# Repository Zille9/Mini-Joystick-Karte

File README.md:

# Mini-Joystick-Karte
Joystickkarte für den HIVE-Retrostyle-Computer
Anschluss erfolgt am I2C-BUS des HIVE (PIN18 SCL und PIN19 SDA vom Administra-Chip)

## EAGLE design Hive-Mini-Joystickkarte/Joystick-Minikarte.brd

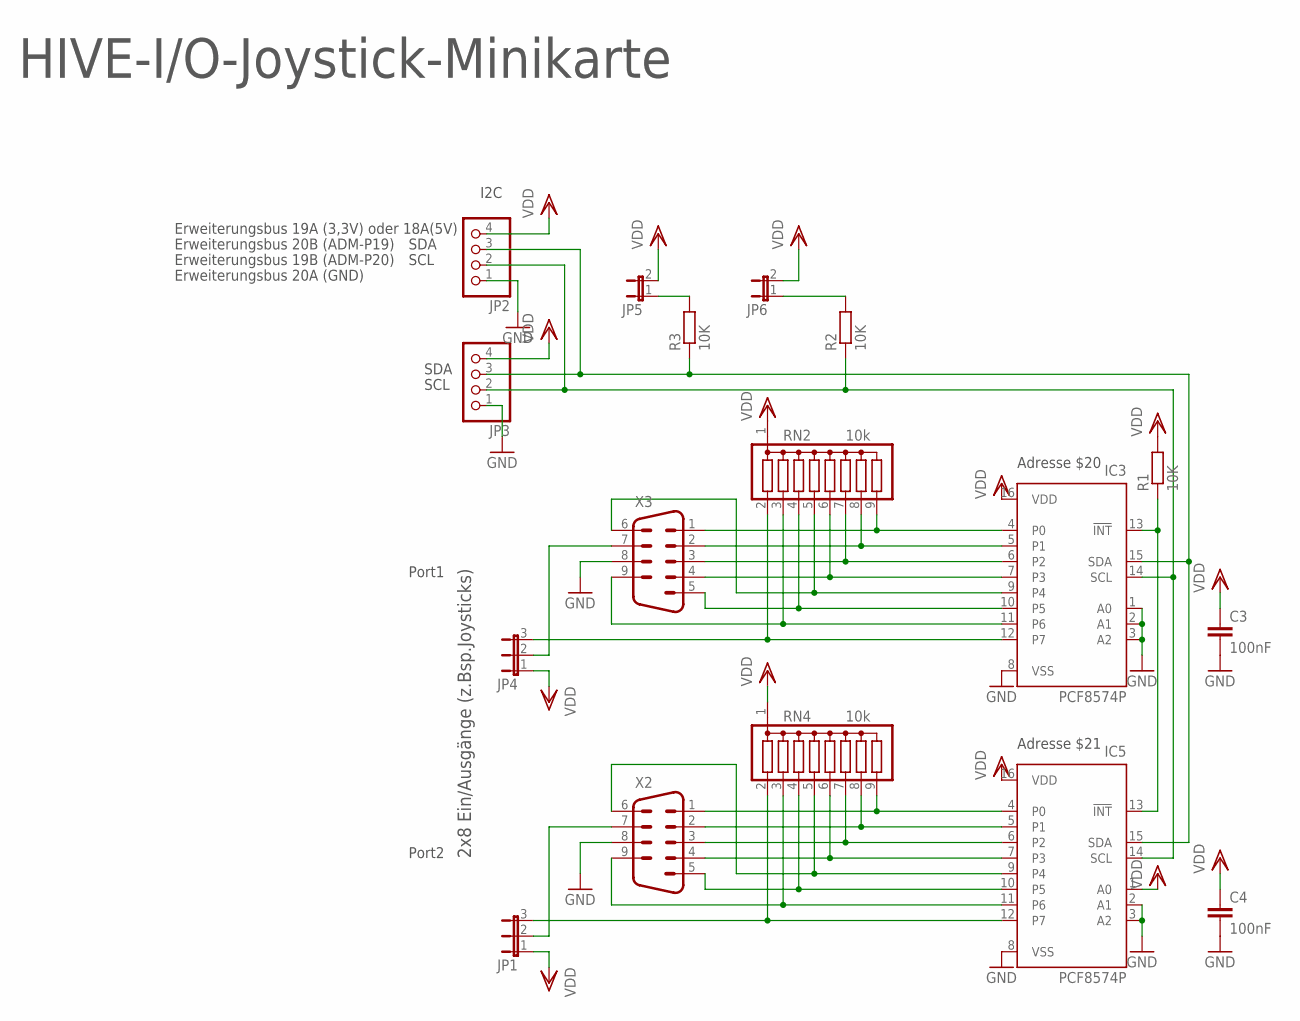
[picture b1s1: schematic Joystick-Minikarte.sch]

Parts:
C3, C4: 100nF; C025-024X044
IC3: PCF8574P; DIL16
IC5: PCF8574P; DIL16; MPN PCF8574PN
JP1, JP4: JP2E; JP2
JP2, JP3: PINHD-1X4; 1X04
JP5, JP6: JP1E; JP1
R1, R2, R3: 10K; 0204/7
RN2, RN4: 10k; SIL9
X2, X3: M09HP

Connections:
GND: C3.2, C4.2, IC3.1 (A0), IC3.2 (A1), IC3.3 (A2), IC3.8 (VSS), IC5.2 (A1), IC5.3 (A2), IC5.8 (VSS), JP2.1, JP3.1, X2.8, X3.8
unnamed: JP4.2, X3.7
unnamed: JP1.2, X2.7
unnamed: JP6.1, R2.2
unnamed: JP5.1, R3.2
unnamed: IC3.15 (SDA), IC5.15 (SDA), JP2.3, JP3.3, R3.1
unnamed: IC3.14 (SCL), IC5.14 (SCL), JP2.2, JP3.2, R2.1
unnamed: IC3.13 (!INT), IC5.13 (!INT), R1.1
unnamed: IC5.4 (P0), RN4.9, X2.1
unnamed: IC5.5 (P1), RN4.8, X2.2
unnamed: IC5.6 (P2), RN4.7, X2.3
unnamed: IC5.7 (P3), RN4.6, X2.4
unnamed: IC5.9 (P4), RN4.5, X2.6
unnamed: IC5.10 (P5), RN4.4, X2.5
unnamed: IC5.11 (P6), RN4.3, X2.9
unnamed: IC5.12 (P7), JP1.3, RN4.2
unnamed: IC3.4 (P0), RN2.9, X3.1
unnamed: IC3.5 (P1), RN2.8, X3.2
unnamed: IC3.6 (P2), RN2.7, X3.3
unnamed: IC3.7 (P3), RN2.6, X3.4
unnamed: IC3.9 (P4), RN2.5, X3.6
unnamed: IC3.10 (P5), RN2.4, X3.5
unnamed: IC3.11 (P6), RN2.3, X3.9
unnamed: IC3.12 (P7), JP4.3, RN2.2
VDD: C3.1, C4.1, IC3.16 (VDD), IC5.1 (A0), IC5.16 (VDD), JP1.1, JP2.4, JP3.4, JP4.1, JP5.2, JP6.2, R1.2, RN2.1, RN4.1

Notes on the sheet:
I2C
SDA
SCL
HIVE-I/O-Joystick-Minikarte
2x8 Ein/Ausgänge (z.Bsp.Joysticks)
Port1
Port2
Erweiterungsbus 20B (ADM-P19)
Erweiterungsbus 19B (ADM-P20)
Erweiterungsbus 20A (GND)
Erweiterungsbus 19A (3,3V) oder 18A(5V)
Adresse $20
Adresse $21

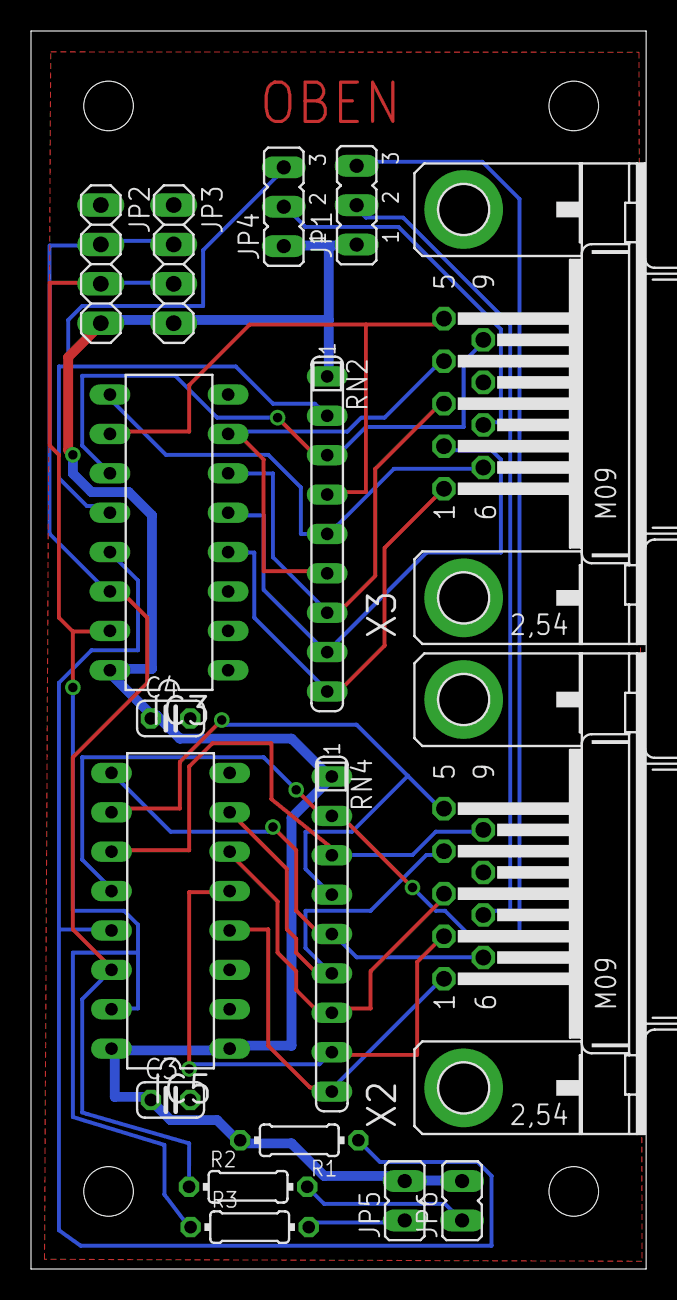
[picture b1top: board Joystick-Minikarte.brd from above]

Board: 2 copper layers, 39.7 x 79.8 mm, 17 parts (0 on the bottom side), 25 nets.
